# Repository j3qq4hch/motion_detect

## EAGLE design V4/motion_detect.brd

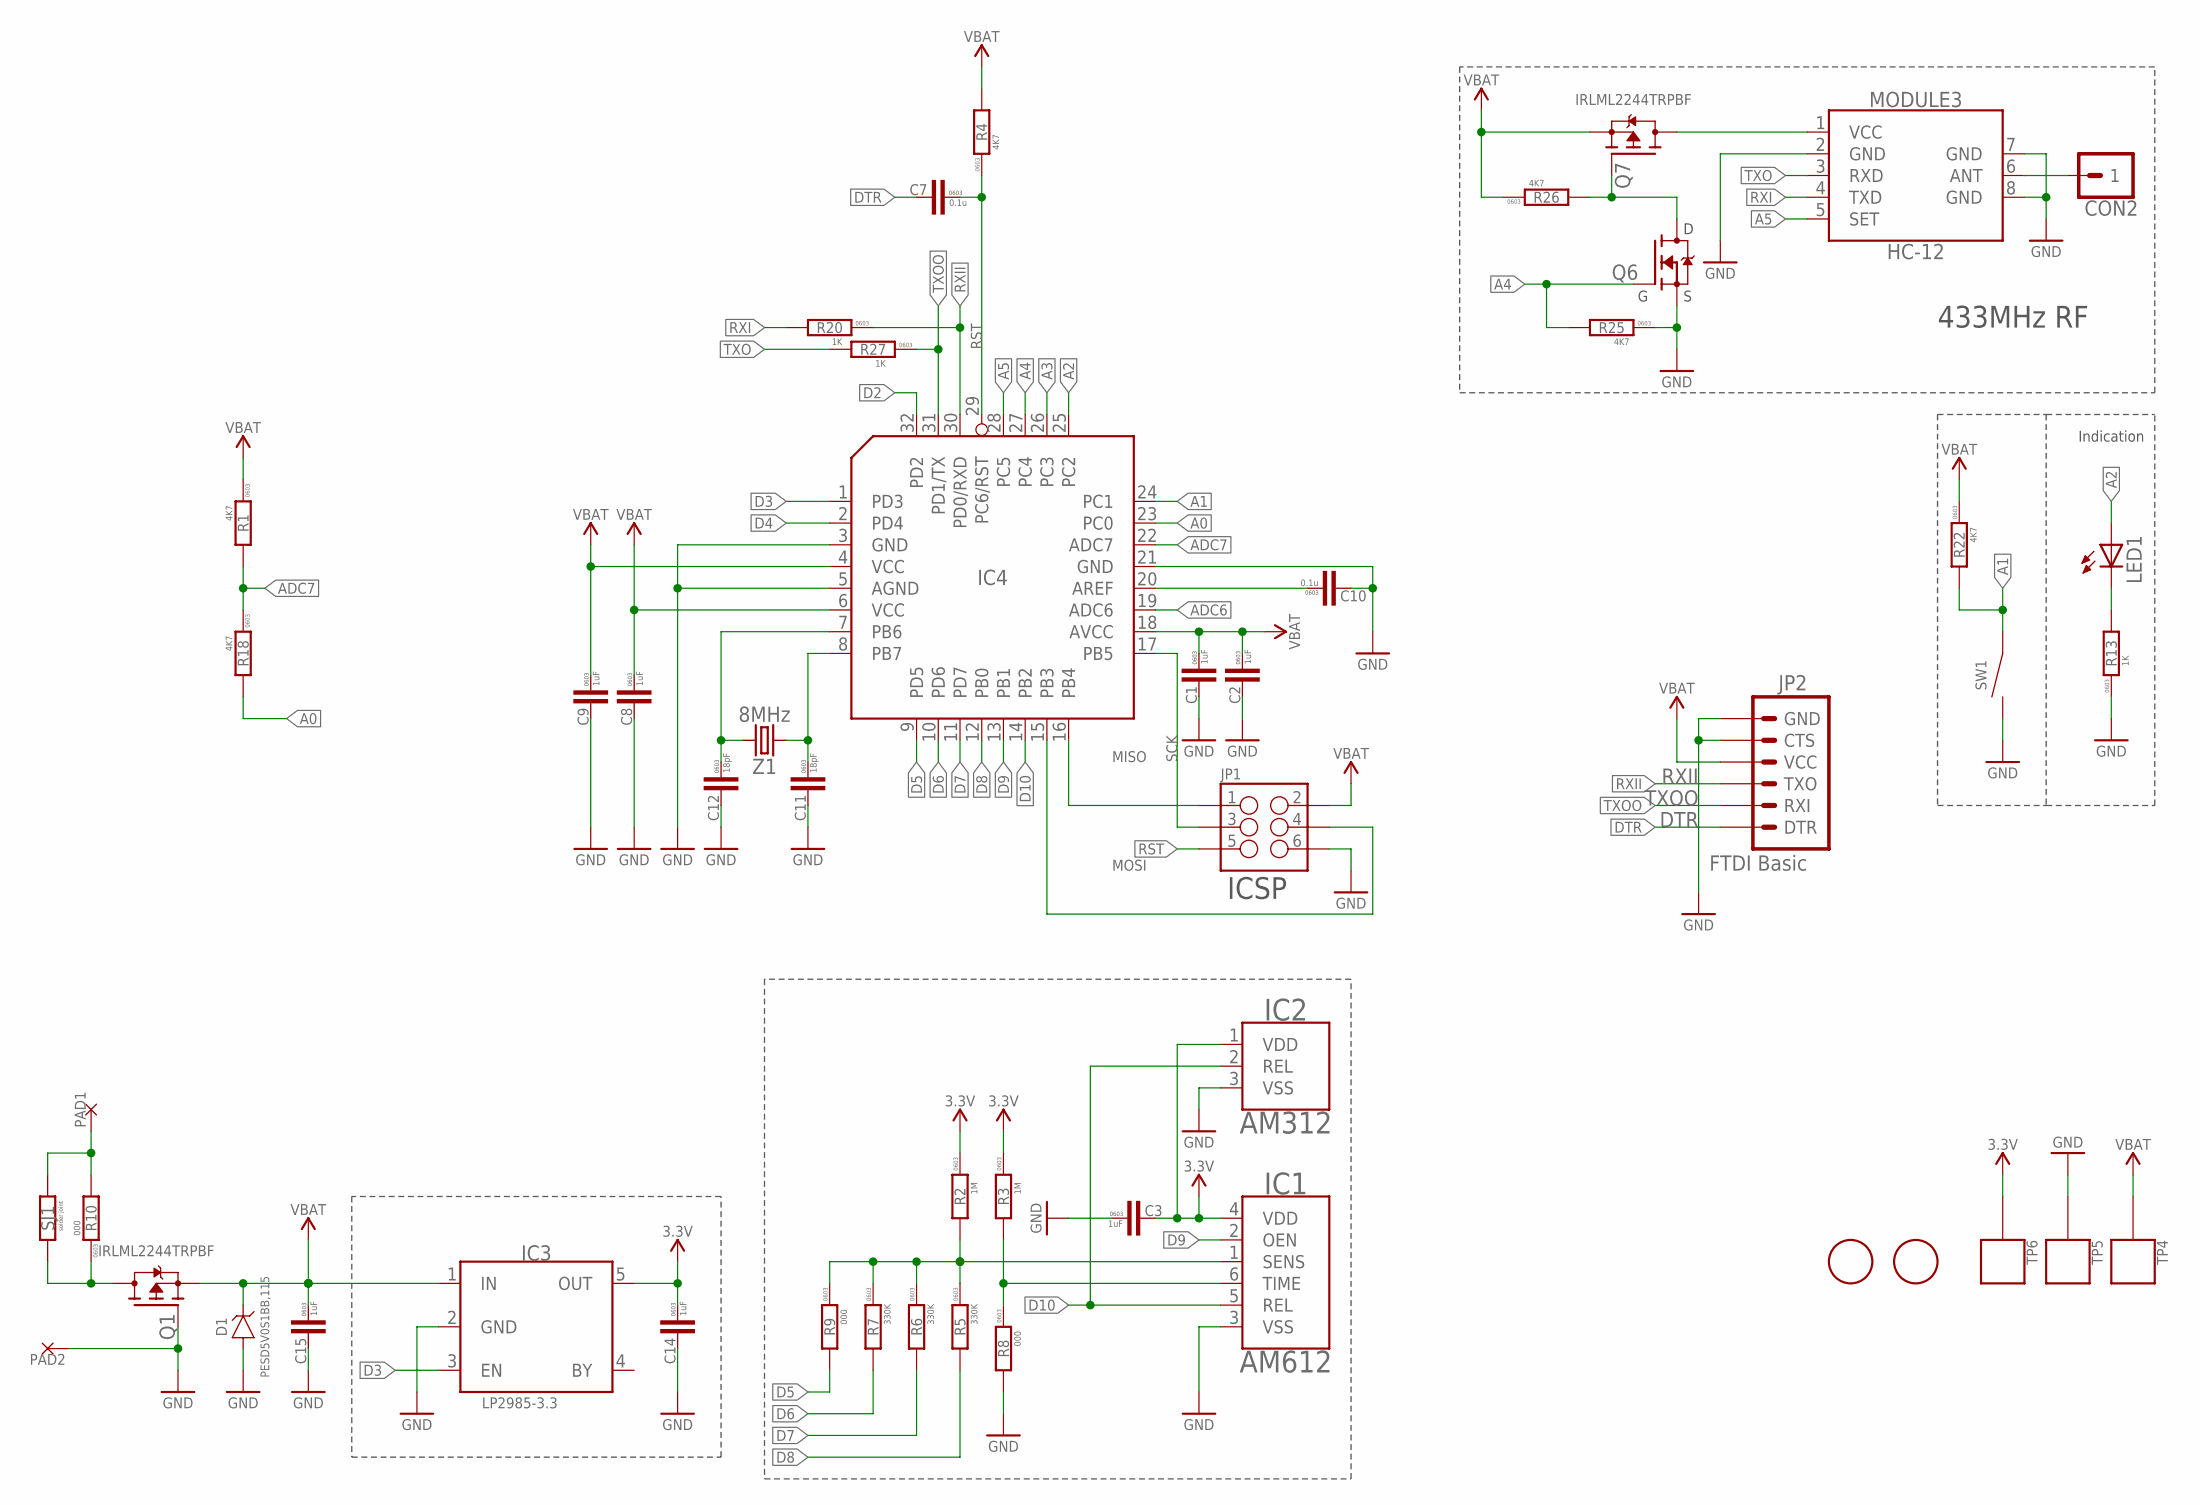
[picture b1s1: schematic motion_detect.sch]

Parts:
C1, C2, C3, C8, C9, C14, C15: 1uF; C0603
C7, C10: 0.1u; C0603
C11, C12: 18pF; C0603
CON2: PINHEAD_1X01-2.54; 1X01-PTH-2.54
D1: PESD5V0S1BB,115; SOD123
IC1: AM612
IC2: AM312; AM312_SIL
IC3: 3.3; SOT23-5L
IC4: ATMEGA168-TQFP32; TQFP32-08
JP1: M03X2POGO_PINS; 2X3_POGO
JP2: FTDI Basic; 1X06
LED1: LED-3MM
MODULE3: HC12; HC-12
PAD1, PAD2: PAD-4X3; 4X3
Q1, Q7: IRLML2244TRPBF; SOT23B-3
Q6: IRLML2502-SOT23; SOT23B-3
R1, R4, R18, R22, R25, R26: 4K7; R0603
R2, R3: 1M; R0603
R5, R6, R7: 330K; R0603
R8, R9, R10: 000; R0603
R13, R20, R27: 1K; R0603
SJ1: SOLDER_JOINT_2P; SJ_2P
SW1: TACT_SWITCH-IT-1102S; IT-1102S
TP4, TP5, TP6: PAD.05; PAD.05X.05; PARTNO *
U$4, U$6: FIDUCIALMOUNT; FIDUCIA-MOUNT
Z1: 8MHz; HC49UP

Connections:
A0: IC4.23 (PC0), R18.2
A1: IC4.24 (PC1), R22.2, SW1.1, SW1.2 (1)
A2: IC4.25 (PC2), LED1.A
A3: IC4.26 (PC3)
A4: IC4.27 (PC4), Q6.1 (G), R25.2
A5: IC4.28 (PC5), MODULE3.5 (SET)
ADC6: IC4.19 (ADC6)
ADC7: IC4.22 (ADC7), R1.2, R18.1
ANT: CON2.1, MODULE3.6 (ANT)
D2: IC4.32 (PD2)
D3: IC3.3 (EN), IC4.1 (PD3)
D4: IC4.2 (PD4)
D5: IC4.9 (PD5), R9.2
D6: IC4.10 (PD6), R7.2
D7: IC4.11 (PD7), R6.2
D8: IC4.12 (PB0), R5.2
D9: IC1.2 (OEN), IC4.13 (PB1)
D10: IC1.5 (REL), IC2.2 (REL), IC4.14 (PB2)
DTR: C7.2, JP2.1 (DTR)
GND: C1.2, C2.2, C3.1, C8.2, C9.2, C10.2, C11.2, C12.2, C14.2, C15.2, D1.A, IC1.3 (VSS), IC2.3 (VSS), IC3.2 (GND), IC4.3 (GND), IC4.5 (AGND), IC4.21 (GND), JP1.P$6 (6), JP2.5 (CTS), JP2.6 (GND), MODULE3.2 (GND), MODULE3.7 (GND), MODULE3.8 (GND), PAD2.P$1, Q1.1 (G), Q6.2 (S), R8.2, R13.1, R25.1, SW1.3 (2), SW1.4 (2), TP5.P$1
MISO: IC4.16 (PB4), JP1.P$1 (1)
MOSI: IC4.15 (PB3), JP1.P$4 (4)
unnamed: PAD1.P$1, R10.2, SJ1.2
unnamed: IC1.6 (TIME), R3.2, R8.1
unnamed: C10.1, IC4.20 (AREF)
unnamed: IC1.1 (SENS), R2.2, R5.1, R6.1, R7.1, R9.1
unnamed: C12.1, IC4.7 (PB6), Z1.2
unnamed: Q1.3 (D), R10.1, SJ1.1
unnamed: C11.1, IC4.8 (PB7), Z1.1
unnamed: LED1.K (C), R13.2
unnamed: MODULE3.1 (VCC), Q7.3 (D)
unnamed: Q6.3 (D), Q7.1 (G), R26.2
RST: C7.1, IC4.29 (PC6/RST), JP1.P$5 (5), R4.1
RXI: MODULE3.4 (TXD), R20.2
RXII: IC4.30 (PD0/RXD), JP2.3 (TXO), R20.1
SCK: IC4.17 (PB5), JP1.P$3 (3)
TXO: MODULE3.3 (RXD), R27.2
TXOO: IC4.31 (PD1/TX), JP2.2 (RXI), R27.1
VBAT: C1.1, C2.1, C8.1, C9.1, C15.1, D1.C, IC3.1 (IN), IC4.4 (VCC), IC4.6 (VCC), IC4.18 (AVCC), JP1.P$2 (2), JP2.4 (VCC), Q1.2 (S), Q7.2 (S), R1.1, R4.2, R22.1, R26.1, TP4.P$1
VDD_3V3: C3.2, C14.1, IC1.4 (VDD), IC2.1 (VDD), IC3.5 (OUT), R2.1, R3.1, TP6.P$1

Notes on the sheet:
433MHz RF
Indication
ICSP

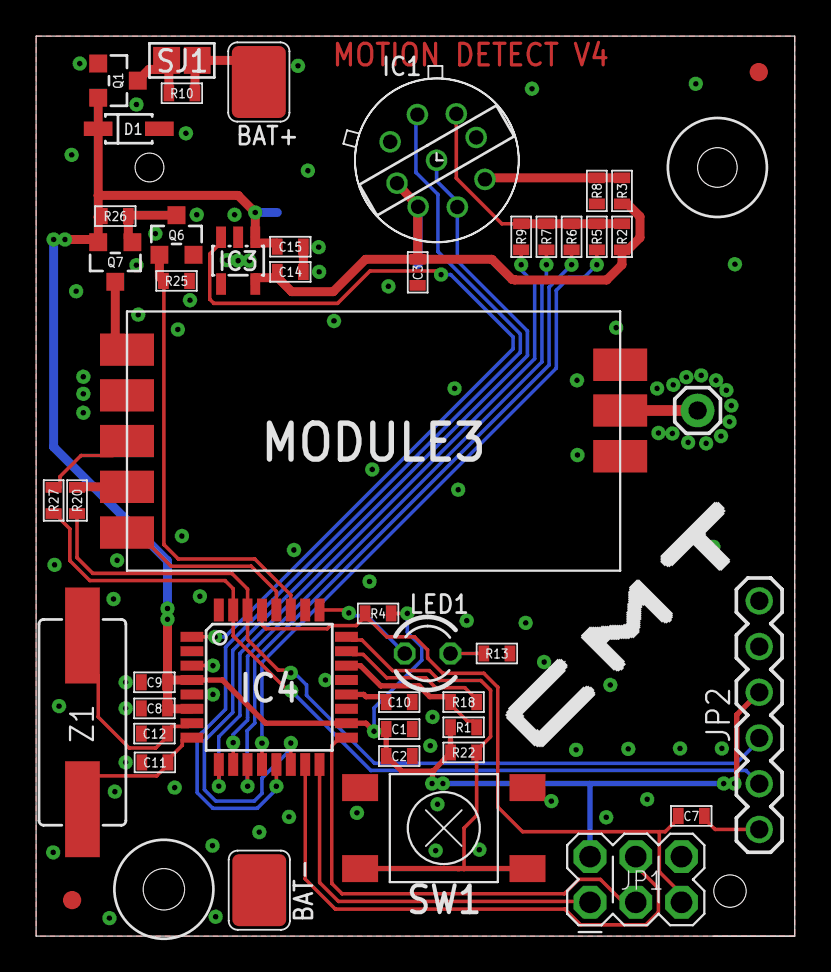
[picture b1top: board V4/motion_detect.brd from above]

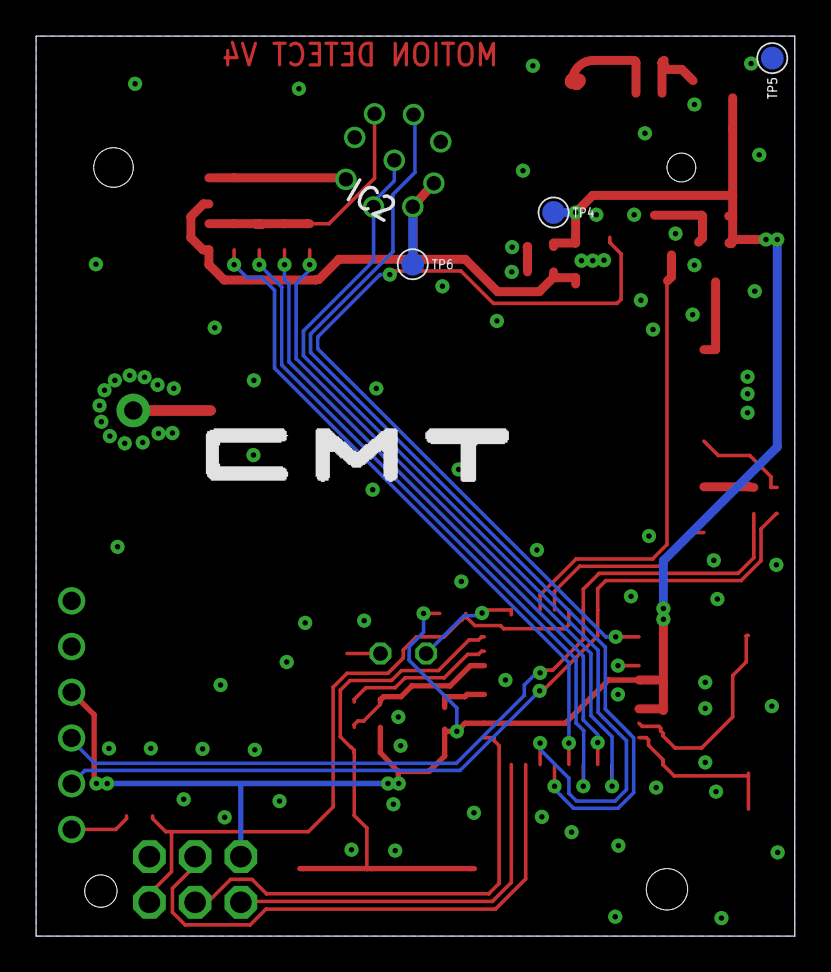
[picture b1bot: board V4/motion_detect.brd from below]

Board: 4 copper layers, 42.1 x 50.0 mm, 54 parts (6 on the bottom side), 36 nets.

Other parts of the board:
U$1, U$3: SMT_LOGO
U$2: REDMOND_BOARD

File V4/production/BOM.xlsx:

Qty | Value | Device | Package | Parts | DIGIKEY# | LINK | MANF | MANF# | Description
1 | RED | LED-3MM | LED-3MM | LED1 |  | https://www.chipdip.ru/product/l-1154id |  |  | Light Emitting Diode
1 |  | M03X2POGO_PINS | 2X3_POGO | JP1 |  | https://www.chipdip.ru/product/pbd-6 |  |  | 2x3 .1 header."
2 | 0.1u | C-0603 | C0603 | C7, C10 |  | https://www.chipdip.ru/product0/9000410929
3 | 0 | R-0603 | R0603 | R8, R9, R10 |  | https://www.chipdip.ru/product0/9000070541
2 | 32pF | C-0603 | C0603 | C11, C12 |  | https://www.chipdip.ru/product/grm1885c1h300j
3 | 1K | R-0603 | R0603 | R13, R20, R27 |  | https://www.chipdip.ru/product0/9000079676
2 | 1M | R-0603 | R0603 | R2, R3 |  | https://www.chipdip.ru/product0/9000079784
7 | 1uF | C-0603 | C0603 | C1, C2, C3, C8, C9, C14, C15 |  | https://www.chipdip.ru/product/grm188r61a105k
1 |  | LP2985-3.3V | SOT23-5L | IC3 | 296-18476-1-ND | https://www.chipdip.ru/product/lp2985-33dbvr | Texas Instruments | LP2985-33DBVR | IC REG LDO 3.3V 0.15A SOT23-5
6 | 4K7 | R-0603 | R0603 | R1, R4, R18, R22, R25, R26 |  | https://www.chipdip.ru/product0/9000079728
1 | 8MHz | CRYSTAL-8MHZHC49UP | HC49UP | Z1 | 535-10212-1-ND | https://www.chipdip.ru/product/8mhz-hc-49sm | Abracon LLC | ABLS-8.000MHZ-B4-T
1 | AM612 | AM612 | AM612 | IC1
1 | ATMEGA168-TQFP32 | ATMEGA168-TQFP32 | TQFP32-08 | IC4 |  | https://www.chipdip.ru/product/atmega168pa-au |  | ATMEGA168
1 | FTDI Basic | ARDUINO_SERIAL_PROGRAMPTH | 1X06 | JP2 |  | https://www.chipdip.ru/product/pls-6
1 | HC12 | HC12 | HC-12 | MODULE3
2 | IRLML2244TRPBF | IRLML2244TRPBF | SOT23B-3 | Q1, Q7 | IRLML2244TRPBFCT-ND | https://www.chipdip.ru/product/irlml2244trpbf | Infineon Technologies | IRLML2244TRPBF | MOSFET P-CH 20V 4.3A SOT23
1 | IRLML2502-SOT23 | IRLML2502-SOT23 | SOT23B-3 | Q6 | IRLML2502PBFTR-ND | https://www.chipdip.ru/product/irlml2502tr | Infineon Technologies | IRLML2502TRPBF | MOSFET N-CH 20V 4.2A SOT-23
1 | PESD5V0S1BB,115 | PESD5V0S1BB,115 | SOD123 | D1 | 1727-3838-2-ND | https://www.chipdip.ru/product/pesd5v0s1ba.115 | Nexperia USA Inc | PESD5V0S1BB,115
1 | TACT_SWITCH-IT-1102S | TACT_SWITCH-IT-1102S | IT-1102S | SW1 |  | https://www.chipdip.ru/product/kls7-ts6604-4.3-180-b-it-1102s
3 | 330K | R-0603 | R0603 | R5, R6, R7 |  | https://www.chipdip.ru/product0/9000079772

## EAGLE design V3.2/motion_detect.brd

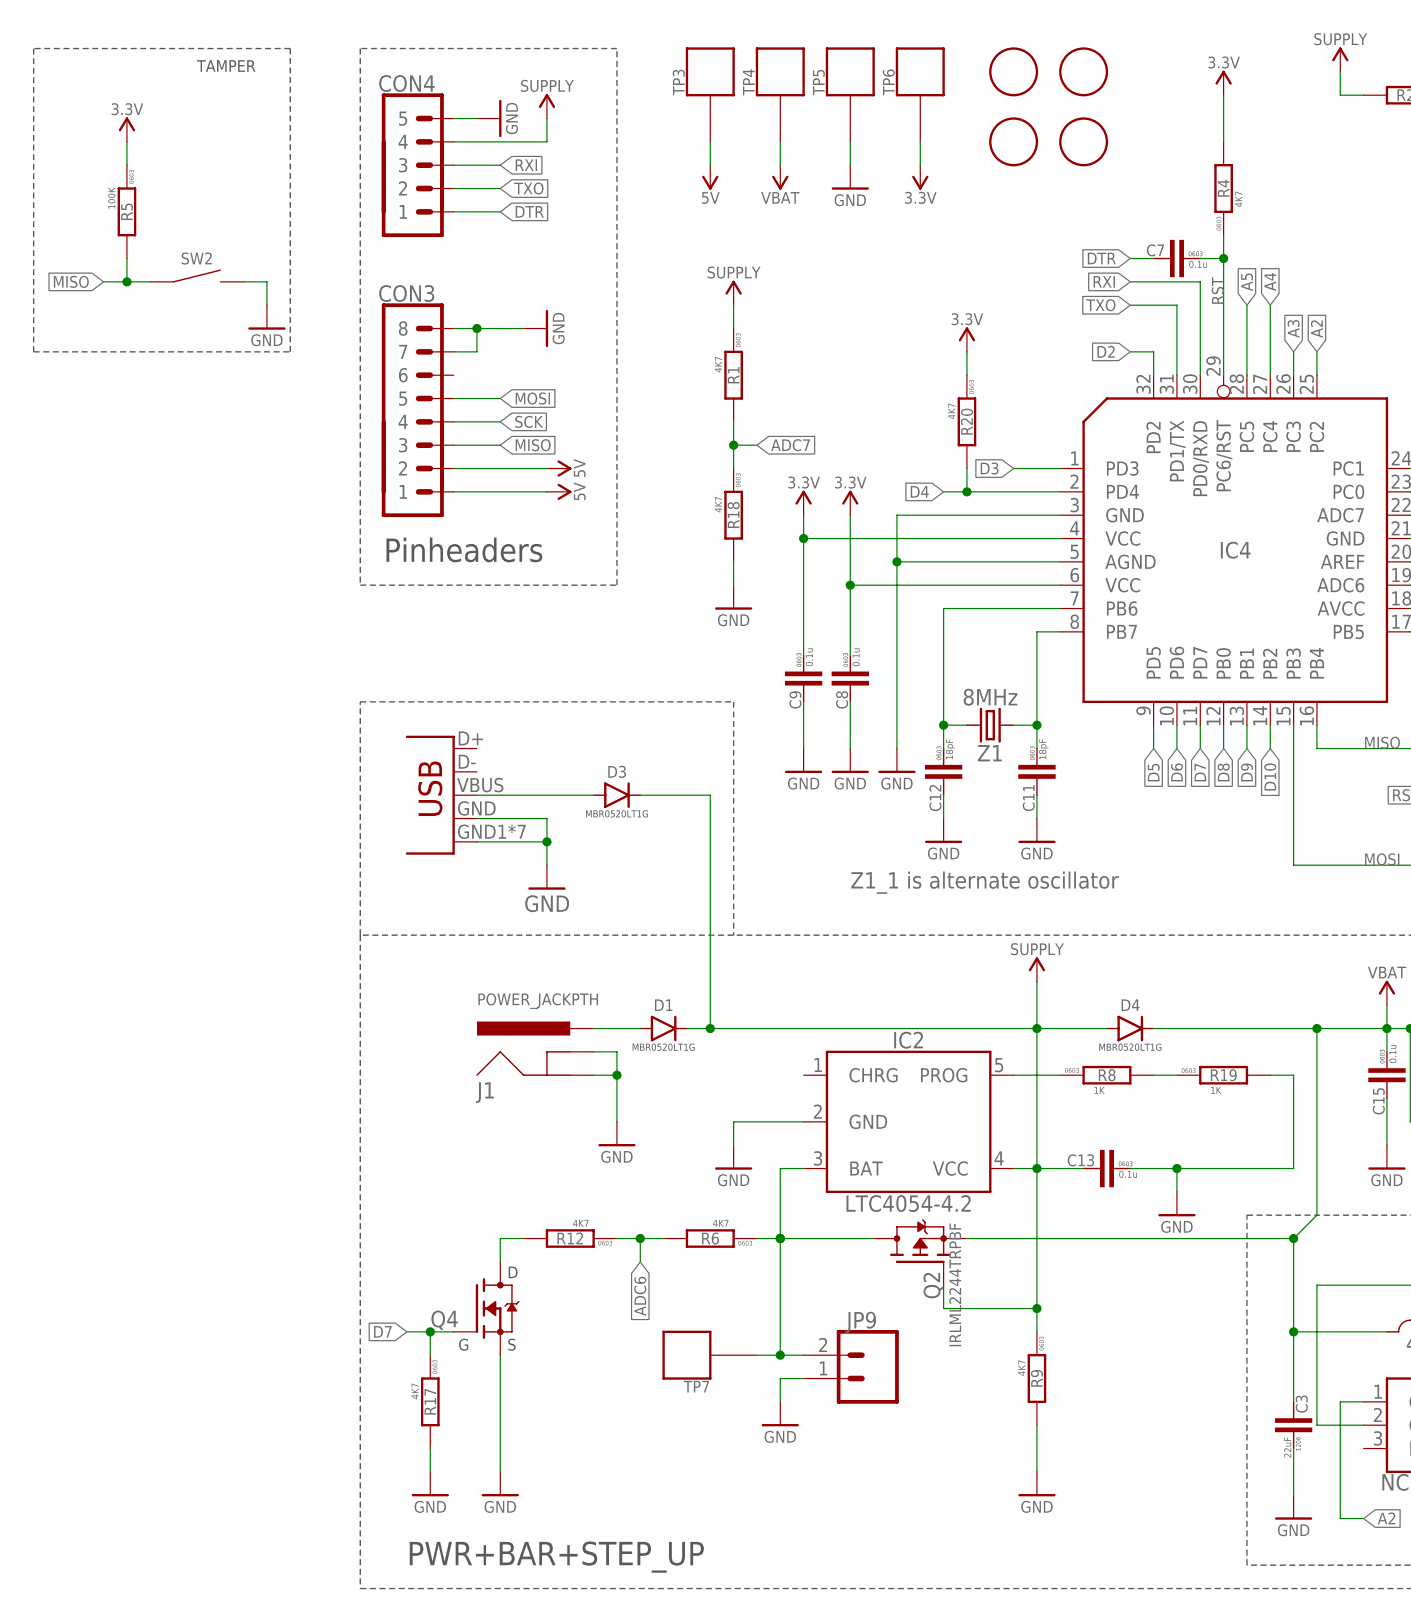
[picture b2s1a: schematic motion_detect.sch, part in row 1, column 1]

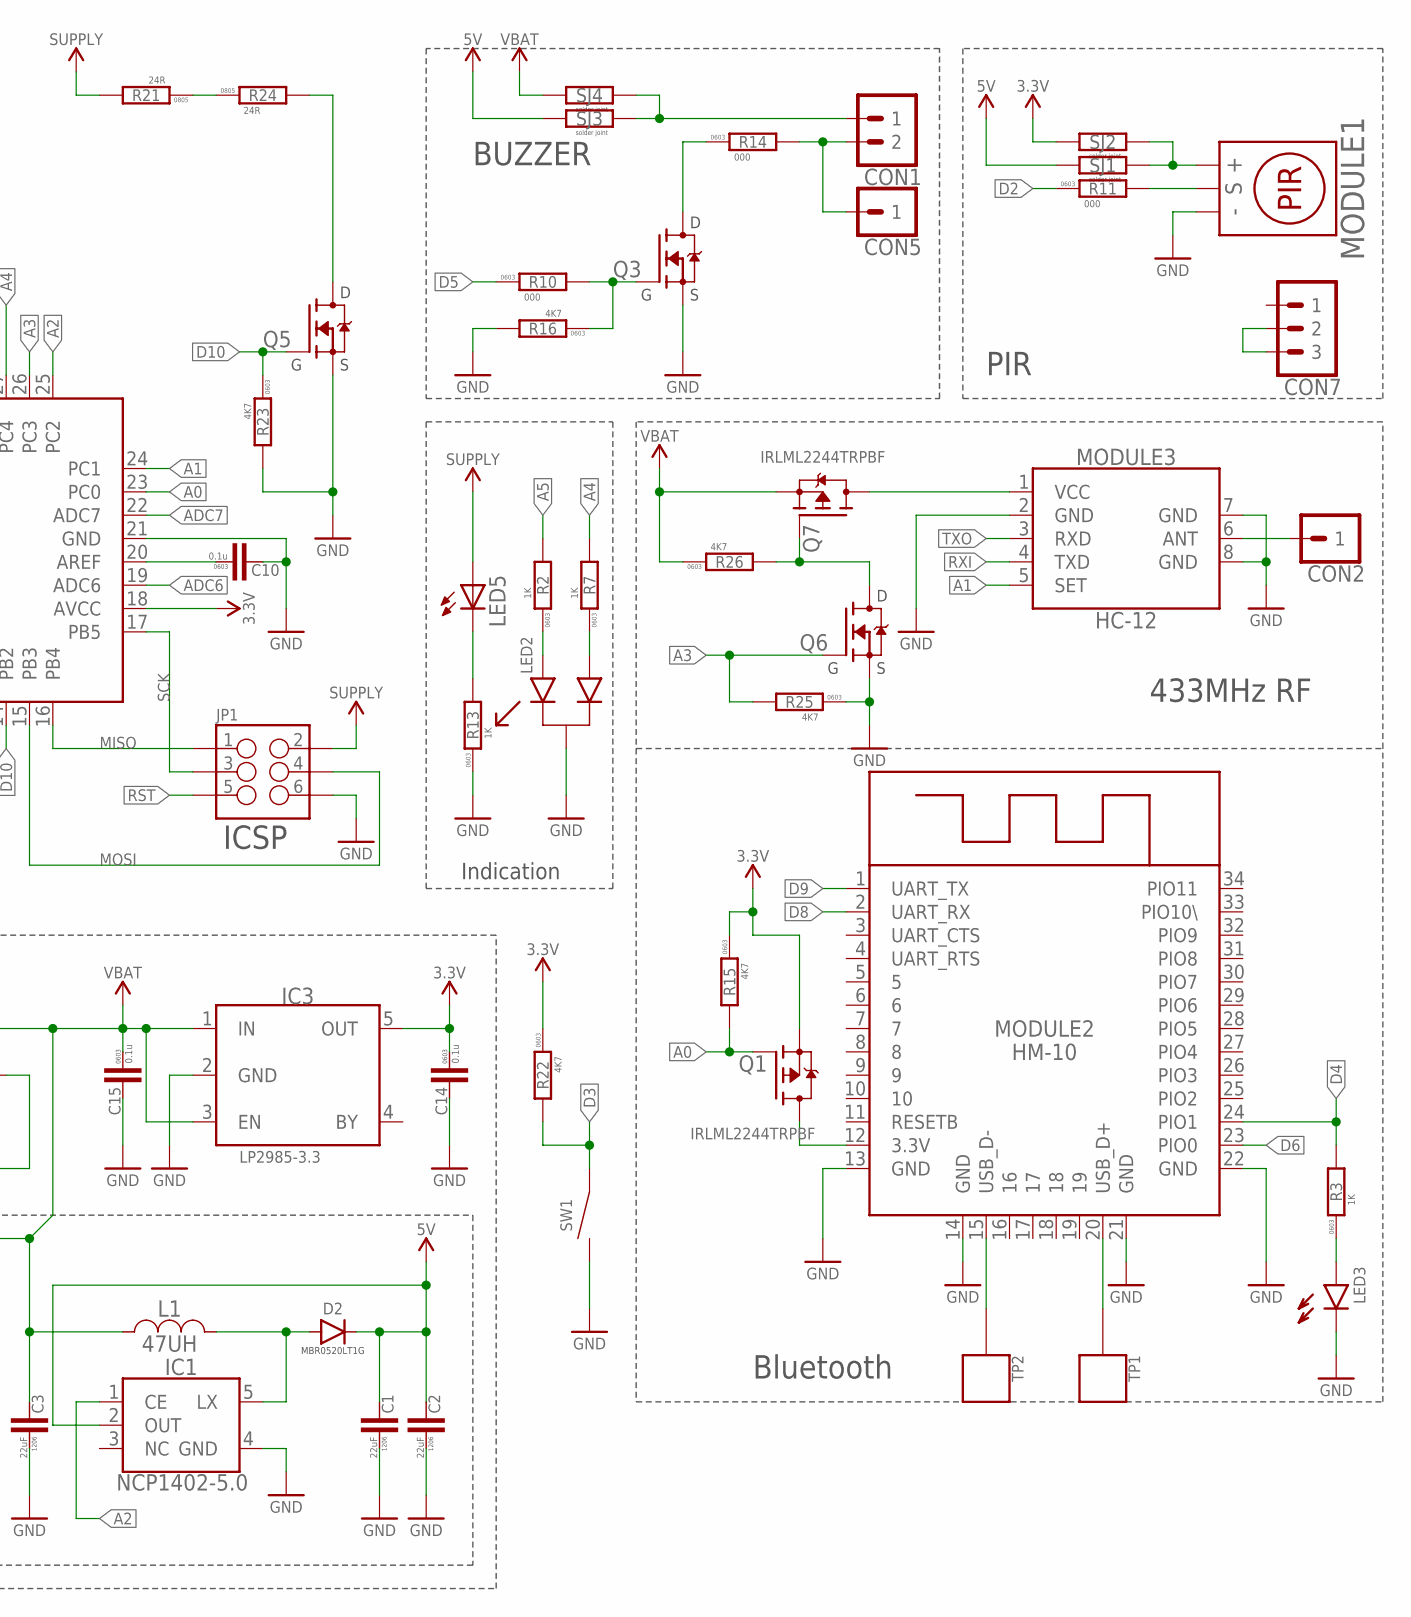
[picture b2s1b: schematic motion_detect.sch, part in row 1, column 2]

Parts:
C1, C2, C3: 22uF; C1206
C7, C8, C9, C10, C13, C14, C15: 0.1u; C0603
C11, C12: 18pF; C0603
CON1: PINHEAD_1X02-2.54; 1X02-PTH-2.54
CON2, CON5: PINHEAD_1X01-2.54; 1X01-PTH-2.54
CON3: PINHEAD_1X08-2.54; 1X08-PTH-2.54
CON4: PINHEAD_1X05-2.54; 1X05-PTH-2.54
CON7: PINHEAD_1X03-2.54; 1X03-PTH-2.54
CON8: USB-1; MICRO_USB_WITH_PEGS
D1, D2, D3, D4: MBR0520L-SOD123; SOD123
IC1: 5.0; SOT23-5
IC2: LTC4054; SOT23-5L
IC3: 3.3; SOT23-5L
IC4: ATMEGA168-TQFP32; TQFP32-08
J1: POWER_JACKPTH; POWER_JACK_PTH
JP1: M03X2POGO_PINS; 2X3_POGO
JP9: M02-B2B-PH-K-S; JST-2-PTH
L1: 47UH; SDR0403
LED2: BL-L315EGW; BL-L315
LED3: LED-0603; LED0603
LED5: LED-3MM
MODULE1: MOTION-PIR-DYP-ME003
MODULE2: HM-10
MODULE3: HC12; HC-12
Q1, Q2, Q7: IRLML2244TRPBF; SOT23B-3
Q3, Q4, Q5, Q6: IRLML2502-SOT23; SOT23B-3
R1, R4, R6, R9, R12, R15, R16, R17, R18, R20, R22, R23, R25, R26: 4K7; R0603
R2, R3, R7, R8, R13, R19: 1K; R0603
R5: 100K; R0603
R10, R11, R14: 000; R0603
R21, R24: 24R; R0805
SJ1, SJ2, SJ3, SJ4: SOLDER_JOINT; RES_0
SW1: TACT_SWITCH-TC-206; TC-0206
SW2: TACT_SWITCH; FSM8JH
TP1, TP2, TP3, TP4, TP5, TP6, TP7: PAD.05; PAD.05X.05; PARTNO *
U$3, U$4, U$5, U$6: FIDUCIALMOUNT; FIDUCIA-MOUNT
Z1: 8MHz; HC49UP

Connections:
A0: IC4.23 (PC0), Q1.1 (G), R15.2
A1: IC4.24 (PC1), MODULE3.5 (SET)
A2: IC1.1 (CE), IC4.25 (PC2)
A3: IC4.26 (PC3), Q6.1 (G), R25.2
A4: IC4.27 (PC4), R7.2
A5: IC4.28 (PC5), R2.2
ADC6: IC4.19 (ADC6), R6.2, R12.1
ADC7: IC4.22 (ADC7), R1.2, R18.1
ANT: CON2.1, MODULE3.6 (ANT)
BAT+: IC2.3 (BAT), JP9.2, Q2.3 (D), R6.1, TP7.P$1
D2: IC4.32 (PD2), R11.1
D3: IC4.1 (PD3), R22.2, SW1.1
D4: IC4.2 (PD4), MODULE2.24 (PIO1), R3.2, R20.2
D5: IC4.9 (PD5), R10.1
D6: IC4.10 (PD6), MODULE2.23 (PIO0)
D7: IC4.11 (PD7), Q4.1 (G), R17.1
D8: IC4.12 (PB0), MODULE2.2 (UART_RX)
D9: IC4.13 (PB1), MODULE2.1 (UART_TX)
D10: IC4.14 (PB2), Q5.1 (G), R23.1
DTR: C7.2, CON4.1
GND: C1.P$1 (1), C2.P$1 (1), C3.P$1 (1), C8.2, C9.2, C10.2, C11.2, C12.2, C13.1, C14.2, C15.2, CON3.7, CON3.8, CON4.5, CON8.GND, CON8.GND1 (SHIELD), CON8.GND2 (SHIELD), CON8.GND3 (SHIELD), CON8.GND4 (SHIELD), CON8.ID (SHIELD), CON8.P$1 (SHIELD), CON8.P$2 (SHIELD), IC1.4 (GND), IC2.2 (GND), IC3.2 (GND), IC4.3 (GND), IC4.5 (AGND), IC4.21 (GND), J1.GND, J1.GNDBREAK, JP1.P$6 (6), JP9.1, LED2.C, LED3.C, MODULE1.1 (GND), MODULE2.13 (GND), MODULE2.14 (GND), MODULE2.21 (GND), MODULE2.22 (GND), MODULE3.2 (GND), MODULE3.7 (GND), MODULE3.8 (GND), Q3.2 (S), Q4.2 (S), Q5.2 (S), Q6.2 (S), R9.2, R13.1, R16.2, R17.2, R18.2, R19.2, R23.2, R25.1, SW1.2, SW2.3 (2), SW2.4 (2), TP5.P$1
MISO: CON3.3, IC4.16 (PB4), JP1.P$1 (1), R5.2, SW2.1, SW2.2 (1)
MOSI: CON3.5, IC4.15 (PB3), JP1.P$4 (4)
unnamed: MODULE2.12 (3.3V), Q1.3 (D)
unnamed: LED2.AG (A), R2.1
unnamed: LED3.A, R3.1
unnamed: C10.1, IC4.20 (AREF)
unnamed: D2.A, IC1.5 (LX), L1.P$2 (2)
unnamed: C12.1, IC4.7 (PB6), Z1.2
unnamed: R8.2, R19.1
unnamed: C11.1, IC4.8 (PB7), Z1.1
unnamed: IC2.5 (PROG), R8.1
unnamed: CON8.VBUS, D3.A
unnamed: MODULE1.2 (OUT), R11.2
unnamed: LED5.K (C), R13.2
unnamed: D1.A, J1.PWR
unnamed: CON7.2, CON7.3
unnamed: Q3.1 (G), R10.2, R16.1
unnamed: MODULE2.15 (USB_D-), TP2.P$1
unnamed: MODULE1.3 (VCC), SJ1.2, SJ2.2
unnamed: MODULE2.20 (USB_D+), TP1.P$1
unnamed: R21.1, R24.1
unnamed: Q3.3 (D), R14.1
unnamed: Q4.3 (D), R12.2
unnamed: CON1.1, SJ3.2, SJ4.2
unnamed: CON1.2, CON5.1, R14.2
unnamed: MODULE3.1 (VCC), Q7.3 (D)
unnamed: Q5.3 (D), R24.2
unnamed: LED2.AR (A1), R7.1
unnamed: Q6.3 (D), Q7.1 (G), R26.2
RST: C7.1, IC4.29 (PC6/RST), JP1.P$5 (5), R4.1
RXI: CON4.3, IC4.30 (PD0/RXD), MODULE3.4 (TXD)
SCK: CON3.4, IC4.17 (PB5), JP1.P$3 (3)
SUP: C13.2, CON4.4, D1.C, D3.C, D4.A, IC2.4 (VCC), JP1.P$2 (2), LED5.A, Q2.1 (G), R1.1, R9.1, R21.2
TXO: CON4.2, IC4.31 (PD1/TX), MODULE3.3 (RXD)
VBAT: C3.P$2 (2), C15.1, D4.C, IC3.1 (IN), IC3.3 (EN), L1.P$1 (1), Q2.2 (S), Q7.2 (S), R26.1, SJ4.1, TP4.P$1
VDD_3V3: C8.1, C9.1, C14.1, IC3.5 (OUT), IC4.4 (VCC), IC4.6 (VCC), IC4.18 (AVCC), Q1.2 (S), R4.2, R5.1, R15.1, R20.1, R22.1, SJ2.1, TP6.P$1
VDD_5V: C1.P$2 (2), C2.P$2 (2), CON3.1, CON3.2, D2.C, IC1.2 (OUT), SJ1.1, SJ3.1, TP3.P$1

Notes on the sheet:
BUZZER
433MHz RF
Bluetooth
PWR+BAR+STEP_UP
Pinheaders
Indication
ICSP
PIR
Z1_1 is alternate oscillator
TAMPER

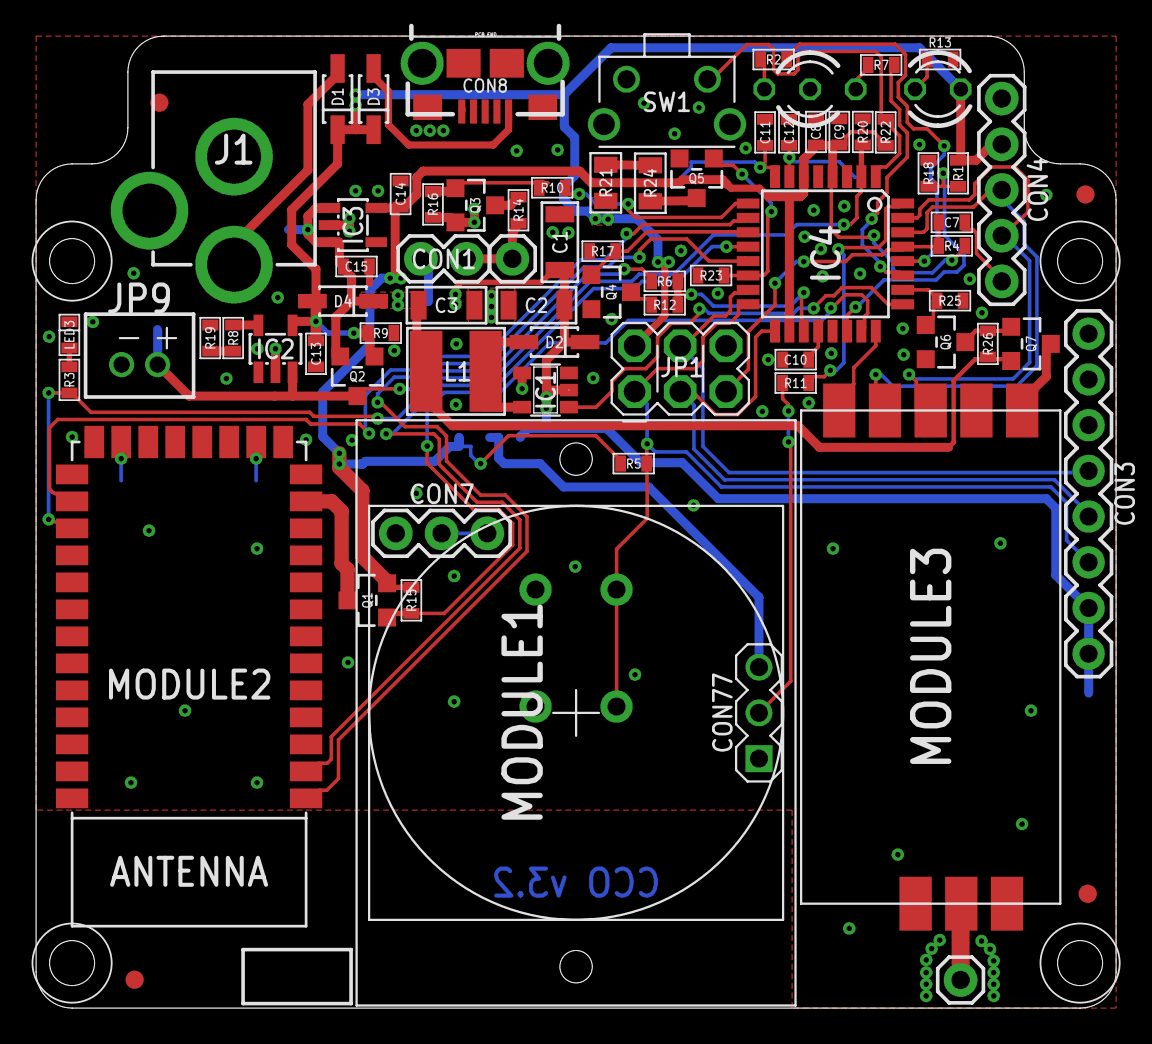
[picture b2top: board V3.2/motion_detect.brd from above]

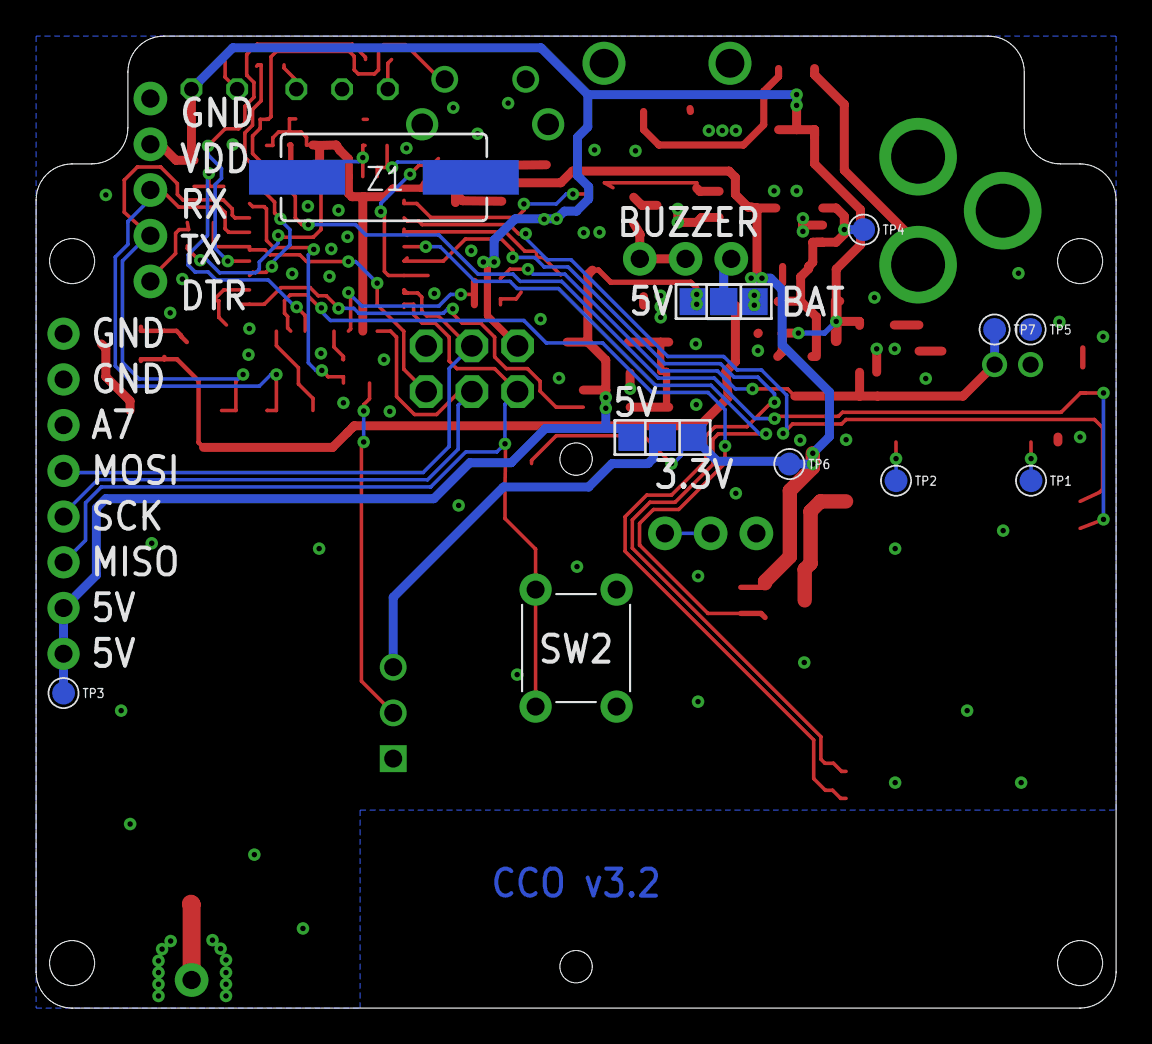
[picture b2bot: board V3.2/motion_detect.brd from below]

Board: 2 copper layers, 60.0 x 54.0 mm, 89 parts (13 on the bottom side), 58 nets.

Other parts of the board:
U$1: BOARD_OUTLINE

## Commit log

2017-05-26 initial import
2017-05-26 deleted unused files
2017-05-30 some minor BOM fixes
2017-07-06 new version
2017-07-10 -update
2017-07-18 -assembly drawings added
2017-08-04 0.1 receiver only
2017-08-09 _for tests on new 70 pcs
2017-08-10 Revert "."
    This reverts commit d78f027b7ecc0f000368222422a274e619fb5248.
2017-08-11 idle_1s у reciever
2017-08-11 чеки
2017-08-14 led: red->red/green
2017-08-16 BLAH
2017-08-16 Fixed silkscreeen
2017-08-17 device_ID_length; trye_to_add
2017-08-17 1
    1
2018-05-07 impport of everything
2018-05-07 some more stuff import
2018-05-08 vias update
2018-05-14 Production files added

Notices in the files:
parts and their libraries:
diy-modules: Released under the Creative Commons Attribution 4.0 International License: http://creativecommons.org/licenses/by/4.0
SparkFun-Connectors: Licensing: CC v3.0 Share-Alike You are welcome to use this library for commercial purposes.
